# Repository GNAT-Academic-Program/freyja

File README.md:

# Freyja

An FPGA development board intended to remove the setup work between an idea
and a working project: independent memory ports, a USB board controller,
observable power rails and keyed extension connectors.

The repository is **Freyja**; the current hardware stamp is **FREYA HW
0.1.0-proto.1**, with **XC7A100T-2FGG676I + RP2350B**. Identity comes from
[`tools/identity.py`](tools/identity.py). The KiCad basename `odin` and imported
library names are retained for compatibility; they do not identify another
active project.

## Open the current project

Open **[`kicad/odin.kicad_pro`](kicad/odin.kicad_pro)** in KiCad 9.
[`kicad/odin.kicad_pcb`](kicad/odin.kicad_pcb) owns placement and routing;
[`kicad/odin.kicad_sch`](kicad/odin.kicad_sch) is the generated root schematic.
See [the project map](kicad/README.md) and the single
[current workflow](ref/ide-agent-prompt.md) before editing or regenerating.

The board is 100 × 140 mm with eight copper layers and 524 parts, each in the
netlist and placed on the PCB, the four mounting holes H1–H4 included. All
assembly is on F.Cu. **Routing is unfinished.** All four PSRAM ports, their
ground connections and return stitching, the `+1V8_IO` distribution, the SDRAM,
the four HDMI pairs, LINK P and Q, the four Ethernet pairs and U30's local supplies,
straps and crystal are on the board, and since 2026-11-09 the regulator cells
U11 to U15, the `+1V0`, `+1V8`, `+2V5`, `VCCIO_1` and `VCCIO_2` distributions,
U34's source-select cell with its control lines, the `+5V` distribution and
its monitor, and the power-input tree (J50 and USB-C to `VSYS`, `VBUS` to U26
and U34, `VSYS` to U11 and U12, U26's and U18's islands), and since 2026-11-10 the
board controller's bring-up set (U7's regulator, crystal, flash, +3V3 and +1V1, the
USB data pair, the supervisor JTAG and sideband, the FPGA configuration straps
and configuration flash, the system clock), then its leftovers (SWD, RUN, UART, heartbeat LED, the USB
TVS, `EXT_EN` to U22), the `DBG_TCK`/`DBG_TDO` and FPGA-to-supervisor UART links, and every `+3V3` and ground
plane connection, then the first FPGA escape batch: the UART's receive line (on a moved ball), the microSD
and MRAM pull-ups with two lines of each to the FPGA, both buffered buses' connector side and three lines of
bus 1's FPGA side, HDMI management and `MON_2V5`; then the signal batch on a revised allocation: 43 of the 48
slot E to H lines (E/F and G/H trade ball rows in bank 34), `HDMI_SDA` (on a moved ball), the whole microSD
and debug JTAG links and `MRAM_SI`, and bus 1's connector side but two lines (U10's channels reversed).
Slots A to D, both buses' FPGA side, `MRAM_CS` and `MON_3V3` remain open: the west half of the FPGA has no
way out past the finished memory and `VCCIO_1` routes, and moving the nine SDRAM address lanes was tried and
does not fit. Counts, the per-face escape results, the leftovers with their alternatives and open issues are in
[current findings](findings.md). The gate reports DRC and unrouted items
without gating them, so a passing gate is not a fabrication pass.

Historical baseline, 2026-11-03 cleanup at `3f76447`, before any routing: zero
tracks and vias, 499 unrouted items listed, DRC zero errors and 313 warnings,
zero schematic-parity issues. Independent import/connector checks had
pre-existing failures, listed in the findings.

## Work and validate

Run from the repository root with Python 3, KiCad CLI/pcbnew 9 and PyYAML:

```sh
python3 tools/alloc.py --check
python3 tools/gate.py --strict
python3 tools/audit_easyeda.py
python3 tools/check_connector_rework.py
git diff --check
```

The gate reports DRC/unrouted counts without failing on them. Read the report
and independent checker results. [The workflow](ref/ide-agent-prompt.md)
explains exact ERC expectations, scratch DRC reports, file ownership,
generator writes and the cleanup checkpoint after several routing chunks.
Documentation cleanup must preserve hardware contents. Never use
`tools/gen_pcb.py` without `--rules-only` on the existing board.

Circuit ownership is [`tools/design.py`](tools/design.py); FPGA allocation is
[`tools/alloc.py`](tools/alloc.py). The project uses generated `odin:` libraries,
stock KiCad libraries, and **active imported `EasyEDA:` symbols, footprints and
3D models under [`easyeda/`](easyeda/)**. Preserve their identifiers and exact
qualified land patterns.

## Design intent

Four independent QSPI PSRAM links provide 32 MB without forcing a project to
start with a DDR controller; a 32 MB SDRAM provides another memory option.
The RP2350B is the board controller for configuration, power control and
readback. Eight direct extension sections and two buffered sections expose
documented signals and rails. ETH, raw LVDS LINK P/Q and HDMI are present in
the current circuit. Firmware, timing and operating performance still require
their own validation; PCB/ERC checks alone do not establish them.

For future decisions, keep the original test: **does this remove work that
was never the point, or add work that looks like the point?** Prefer explicit
limits, direct wiring and references an extension builder can understand.

## Supporting references

- [User manual](ref/user-manual.md), [extension connector contract](ref/extension-ux.md) and [worked Gameboy extension](ref/gameboy-extension.md).
- [Parts guide](ref/parts-guide.md), [qualified parts](ref/qualified-parts.md), [power budget](ref/power-budget.md), [assembly/import checklist](ref/jlcpcb-import-checklist.md) and [BOM](ref/bom-jlcpcb.csv).
- [Power input](ref/power-input.md), [power tree](ref/power.md), [PSRAM](ref/psram.md), [controller flash](ref/supervisor-flash.md), [network](ref/network.md) and [raw LVDS links](ref/link-ports.md).
- [Mechanical intent and history](floorplan.md), [FPGA decoupling](ref/decoupling.md), [island layout rationale](ref/island-layouts.md), [impedance/stackup](ref/pcb-impedance.md) and [local datasheets](ref/datasheets/).
- [SDRAM profile, 100 MHz CL3](gateware/sdram100/README.md): implementation contract, timing fixture and constraints, separate from the allocation gate.
- [RGMII profile, 1000 Mb/s](gateware/rgmii1000/README.md): timing contract, fixture and constraints for U30, separate from the allocation gate.
- [Current status and chronological findings](findings.md). Its older numbered findings are dated history, not a fresh open-task list.
- [Archive index and provenance](archive/README.md): old Altium/EasyEDA exports, extraction reports, superseded workflow/plans, dated review evidence and Vivado scratch outputs. [Salvage rationale](ref/salvage-from-odin0.md) retains useful earlier engineering decisions.

std::vector<int> a; --- stree

std::vector<int> b; --- forge

type int_vector std::vector<int, float>;

a: int_vector;
b: int_vector;

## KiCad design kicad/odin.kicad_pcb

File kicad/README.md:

# Current FREYA KiCad project

Open **[odin.kicad_pro](odin.kicad_pro)** in KiCad 9. The hardware is **FREYA
HW 0.1.0-proto.1**, XC7A100T-2FGG676I + RP2350B; `odin` is the retained project
basename. **[odin.kicad_pcb](odin.kicad_pcb) is the authoritative manual
layout.** Preserve its placement, routing, outline, zones and mounting holes.

Use the single [current workflow](../ref/ide-agent-prompt.md) for ownership,
checks, regeneration side effects and the recurring cleanup checkpoint.
[Current findings](../findings.md) records the measured baseline and known
check failures. The [root README](../README.md) links subsystem references.

## File map

| File | Role |
|---|---|
| `odin.kicad_pcb` | Live layout; not a disposable generator output. |
| `odin.kicad_pro`, `odin.kicad_dru` | Project settings/net classes and custom design rules. `gen_pcb.py --rules-only` rewrites generated rules plus PCB stackup/layers; it is not a read-only check. |
| `odin.kicad_sch` | Root schematic generated by `tools/gen_project.py` from `tools/design.py`. |
| `fpga.kicad_sch` | FPGA, decoupling and configuration straps. |
| `power.kicad_sch` | Input, source mux, regulators, AUX IN pass-through and monitoring. |
| `memory.kicad_sch` | Four independent 1.8 V PSRAMs, SDRAM, MRAM, microSD and configuration flash. |
| `supervisor.kicad_sch` | Board Controller sheet: RP2350B, USB-C and FPGA control. |
| `slots.kicad_sch` | Eight direct and two buffered sections, rail selection and branch protection. |
| `network.kicad_sch` | RTL8211FDI-CG gigabit PHY/ETH and raw LVDS LINK P/Q. |
| `video.kicad_sch` | HDMI output through TPD12S016. |
| `odin.net` | KiCad export of the generated schematic; PCB synchronization reads this file. |
| `odin.kicad_sym`, `odin.pretty/` | Generated custom project symbols/footprints. |
| `sym-lib-table`, `fp-lib-table` | Select the custom, imported and system libraries. |
| `odin.kicad_prl`, `fp-info-cache` | Retained local editor state/cache; not circuit or layout sources. |

Manual schematic arrangements and generated library edits are overwritten by
regeneration. Read the generator write map before using any writer.
**`tools/gen_pcb.py` without `--rules-only` is prohibited on this board.**
`load_pcb.py` preserves common footprint origins but changes parts/nets and
also runs the silkscreen writer; it does not certify routed copper preservation.

## Imported dependencies and setup

The tables point to **`../easyeda/EasyEDA.kicad_sym`** and
**`../easyeda/EasyEDA.pretty/`**. These are active, qualified imported
dependencies, including U1's FGG676 footprint. Models live in
`../easyeda/EasyEDA.3dshapes/`. Keep the `EasyEDA:` namespace and the exact
footprints. `tools/alloc.py`, `symlib.py`, `gen_kicad.py` and `load_pcb.py`
also reference those paths.

Imported model paths use a mixture of `${KIPRJMOD}`, `${KICAD_3RD_PARTY}` and
relative `easyeda/` paths. Where used, configure `KICAD_3RD_PARTY` to the
repository's `easyeda` directory in KiCad's path settings; it is unset in the
verification shell. Six of the live board's 39 distinct imported model paths
also name files absent from the repository even with that mapping (DFN-10,
ESOP-8, QFN-20, RJ45 L16.5, SMB L4.32 and WSON-8 L2.0). This is a pre-existing
3D-preview dependency gap. Relative `easyeda/` paths may require resolution
from the repository root. Cleanup preserves all model identifiers and files.
Stock symbols, footprints
and optional stock 3D models come from the KiCad installation. The small
`kicad/EasyEDA.*` copies remain in place; the project tables select the
`../easyeda/` versions. Do not treat their presence as another active project.

## Current layout and references

The outline is 100 × 140 mm with 2 mm corner chamfers, eight layers, ENIG,
nominal 1.6 mm, JLC08161H-1080A: S / GND / S / PWR / GND / S / GND / S. The PCB
has 524 footprints, one per netlist part (the mounting holes H1–H4 included since 2026-11-10), all origins in the
outline's bounding box and all assembly on F.Cu. Five zones: GND on In1/In4/In6,
and +3V3 plus the +1V0 island on In3. Routing is under way and unfinished;
current counts are in [findings](../findings.md). At the 2026-11-03 cleanup
baseline `3f76447` the board had no tracks or vias.

Read [impedance and routing constraints](../ref/pcb-impedance.md),
[floorplan/mechanical intent](../floorplan.md),
[island layouts](../ref/island-layouts.md),
[decoupling](../ref/decoupling.md) and
[parts guide](../ref/parts-guide.md) alongside the actual board. Planning SVGs
and city YAML are design aids, not current placement snapshots. RGMII's
0.125 mm geometry remains an estimate to confirm with the fabricator.

Run the [validation commands](../ref/ide-agent-prompt.md#checks-that-do-not-write-hardware)
from the repository root. Exact ERC expectation: zero errors and the two
`FPGA_DXP`/`FPGA_DXN` dangling-label warnings, enforced by `tools/check_erc.py`.
The gate passes at the cleanup baseline, but DRC warnings/unrouted counts and
the independent checker failures still need review; see
[current findings](../findings.md). Dated verification counts and superseded
plans live in [the archive](../archive/README.md).

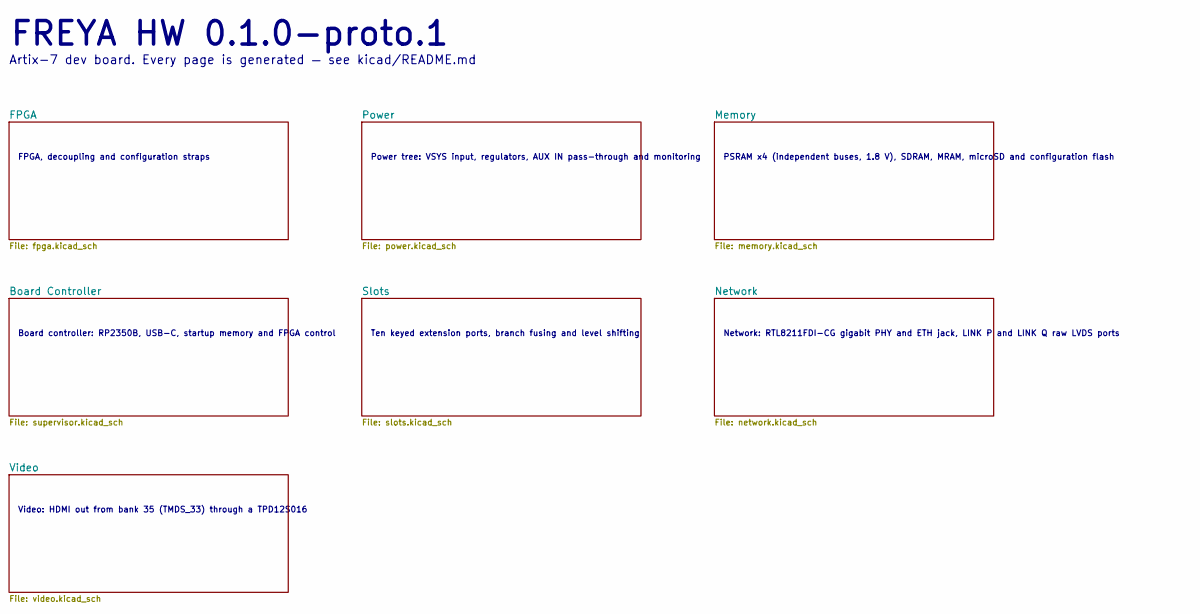
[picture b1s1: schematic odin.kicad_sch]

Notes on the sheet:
FREYA HW 0.1.0-proto.1
Artix-7 dev board. Every page is generated — see kicad/README.md
FPGA, decoupling and configuration straps
Power tree: VSYS input, regulators, AUX IN pass-through and monitoring
PSRAM x4 (independent buses, 1.8 V), SDRAM, MRAM, microSD and configuration flash
Board controller: RP2350B, USB-C, startup memory and FPGA control
Ten keyed extension ports, branch fusing and level shifting
Network: RTL8211FDI-CG gigabit PHY and ETH jack, LINK P and LINK Q raw LVDS ports
Video: HDMI out from bank 35 (TMDS_33) through a TPD12S016

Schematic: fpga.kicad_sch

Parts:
C246, C328: 100nF; C_0402_1005Metric; LCSC C1525
C301: 330uF 6.3V T520V337M006ATE025; CP_EIA-7343-31_Kemet-D; LCSC C136150
C302, C303, C304, C305, C306, C307, C320, C321, C322, C330, C331, C336, C337, C342, C343, C348, C349, C354, C355, C360, C361: 4.7uF 6.3V; C_0805_2012Metric
C308, C309, C310, C311, C312, C313, C314, C315, C317, C318, C323, C324, C325, C326, C327, C332, C333, C334, C335, C338, C339, C340, C341, C344, C345, C346, C347, C350, C351, C352, C353, C356, C357, C358, C359, C362, C363, C364, C365: 0.47uF 6.3V; C_0603_1608Metric
C316: 100uF 2.5V; C_1210_3225Metric
C319, C329, C366, C367, C368, C369, C394: 47uF 6.3V; C_1210_3225Metric
D1: F.0603.00025/P2-0603G1TS2-06T-002; LED0603-RD_GREEN; LCSC C7496818
Q4: BSS138LT1G; SOT-23-3_L2.9-W1.6-P1.90-LS2.8-BR; LCSC C82045
R1, R2, R3, R6: 1k; R_0402_1005Metric; LCSC C11702
R4, R5, R98, R203: 4.7k; R_0402_1005Metric; LCSC C25900
R7: 330; R_0402_1005Metric
R147: 33; R_0402_1005Metric; LCSC C25105
U1: XC7A100T-2FGG676I; FBGA-676_L27.0-W27.0-R26-C26-P1.00-BL; LCSC C1521803
X4: 50MHz CMOS; OSC-SMD_4P-L3.2-W2.5-BL; LCSC C717684

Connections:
+1V0: C301.1, C302.1, C303.1, C304.1, C305.1, C306.1, C307.1, C308.1, C309.1, C310.1, C311.1, C312.1, C313.1, C314.1, C315.1, C316.1, C317.1, C318.1, U1.J11 (VCCINT), U1.J13 (VCCINT), U1.K10 (VCCINT), U1.K12 (VCCINT), U1.L11 (VCCINT), U1.L13 (VCCINT), U1.M10 (VCCINT), U1.N13 (VCCBRAM), U1.P10 (VCCINT), U1.R13 (VCCBRAM), U1.T10 (VCCINT), U1.T12 (VCCINT), U1.U11 (VCCINT), U1.U13 (VCCBRAM), U1.V10 (VCCINT), U1.V12 (VCCINT), U1.W13 (VCCBRAM); also elsewhere on the board
+1V8: C319.1, C320.1, C321.1, C322.1, C323.1, C324.1, C325.1, C326.1, C327.1, C328.1, U1.J9 (VCCAUX), U1.L9 (VCCAUX), U1.M12 (VCCADC_0), U1.N9 (VCCAUX), U1.R9 (VCCAUX), U1.U9 (VCCAUX); also elsewhere on the board
+1V8_IO: C330.1, C331.1, C332.1, C333.1, C334.1, C335.1, C394.1, U1.AC25 (VCCO_13), U1.T16 (VCCO_13), U1.T26 (VCCO_13), U1.U23 (VCCO_13), U1.V20 (VCCO_13), U1.Y24 (VCCO_13); also elsewhere on the board
+2V5: C348.1, C349.1, C350.1, C351.1, C352.1, C353.1, C368.1, U1.A21 (VCCO_16), U1.B18 (VCCO_16), U1.C25 (VCCO_16), U1.D22 (VCCO_16), U1.E19 (VCCO_16), U1.F16 (VCCO_16); also elsewhere on the board
+3V3: C246.1, C329.1, C336.1, C337.1, C338.1, C339.1, C340.1, C341.1, C360.1, C361.1, C362.1, C363.1, C364.1, C365.1, C366.1, R1.1, R4.1, R5.1, R6.1, R7.1, R98.1, R203.1, U1.A1 (VCCO_35), U1.AA1 (VCCO_33), U1.AA21 (VCCO_12), U1.AB15 (CFGBVS_0), U1.AB18 (VCCO_12), U1.AC5 (VCCO_33), U1.AD2 (VCCO_33), U1.AD22 (VCCO_12), U1.AE19 (VCCO_12), U1.AF26 (VCCO_12), U1.C5 (VCCO_35), U1.D2 (VCCO_35), U1.F6 (VCCO_35), U1.G3 (VCCO_35), U1.J7 (VCCO_35), U1.K24 (VCCO_14), U1.L21 (VCCO_14), U1.N15 (VCCO_14), U1.N25 (VCCO_14), U1.P22 (VCCO_14), U1.R19 (VCCO_14), U1.U3 (VCCO_33), U1.W7 (VCCO_33), U1.W11 (VCCO_0), U1.W17 (VCCO_12), U1.Y4 (VCCO_33), U1.Y14 (VCCO_0), X4.1 (Tri-state), X4.4 (VDD); also elsewhere on the board
BUS5V0_DIR: U1.U24 (IO_0_13); also elsewhere on the board
BUS5V0_IO0: U1.V26 (IO_L2P_T0_13); also elsewhere on the board
BUS5V0_IO1: U1.W26 (IO_L2N_T0_13); also elsewhere on the board
BUS5V0_IO2: U1.AB26 (IO_L3P_T0_DQS_13); also elsewhere on the board
BUS5V0_IO3: U1.AC26 (IO_L3N_T0_DQS_13); also elsewhere on the board
BUS5V0_IO4: U1.U25 (IO_L1P_T0_13); also elsewhere on the board
BUS5V0_IO5: U1.U26 (IO_L1N_T0_13); also elsewhere on the board
BUS5V0_IO6: U1.W25 (IO_L4P_T0_13); also elsewhere on the board
BUS5V0_IO7: U1.Y26 (IO_L4N_T0_13); also elsewhere on the board
BUS5V0_OE_N: U1.V23 (IO_L10P_T1_13); also elsewhere on the board
BUS5V1_DIR: U1.U17 (IO_25_13); also elsewhere on the board
BUS5V1_IO0: U1.AC24 (IO_L9N_T1_DQS_13); also elsewhere on the board
BUS5V1_IO1: U1.AB24 (IO_L9P_T1_DQS_13); also elsewhere on the board
BUS5V1_IO2: U1.AB25 (IO_L7N_T1_13); also elsewhere on the board
BUS5V1_IO3: U1.Y25 (IO_L5P_T0_13); also elsewhere on the board
BUS5V1_IO4: U1.AA25 (IO_L5N_T0_13); also elsewhere on the board
BUS5V1_IO5: U1.V24 (IO_L6P_T0_13); also elsewhere on the board
BUS5V1_IO6: U1.W24 (IO_L6N_T0_VREF_13); also elsewhere on the board
BUS5V1_IO7: U1.AA24 (IO_L7P_T1_13); also elsewhere on the board
BUS5V1_OE_N: U1.W23 (IO_L10N_T1_13); also elsewhere on the board
CFG_CCLK: U1.H13 (CCLK_0); also elsewhere on the board
CFG_DONE: Q4.1 (G), R98.2, U1.W10 (DONE_0); also elsewhere on the board
CFG_INIT_B: R5.2, U1.V11 (INIT_B_0); also elsewhere on the board
CFG_M0: R1.2, U1.AB7 (M0_0)
CFG_M1: R2.1, U1.Y9 (M1_0)
CFG_M2: R3.1, U1.W9 (M2_0)
CFG_PROG_B: R4.2, U1.AE16 (PROGRAM_B_0); also elsewhere on the board
DBG_TCK: U1.N21 (IO_L13P_T2_MRCC_14); also elsewhere on the board
DBG_TDI: U1.M20 (IO_L8P_T1_D11_14); also elsewhere on the board
DBG_TDO: U1.L20 (IO_L8N_T1_D12_14); also elsewhere on the board
DBG_TMS: U1.N22 (IO_L13N_T2_MRCC_14); also elsewhere on the board
DONE_LED_A: D1.2 (A), R7.2
DONE_LED_K: D1.1 (C), Q4.3 (D)
FLASH_CS_B: R203.2, U1.P18 (IO_L6P_T0_FCS_B_14); also elsewhere on the board
FLASH_D0_MOSI: U1.R14 (IO_L1P_T0_D00_MOSI_14); also elsewhere on the board
FLASH_D1_MISO: U1.R15 (IO_L1N_T0_D01_DIN_14); also elsewhere on the board
FLASH_D2_WP: U1.P14 (IO_L2P_T0_D02_14); also elsewhere on the board
FLASH_D3_HOLD: U1.N14 (IO_L2N_T0_D03_14); also elsewhere on the board
FPGA_DXN: U1.R11 (DXN_0)
FPGA_DXP: U1.R12 (DXP_0)
GND: C246.2, C301.2, C302.2, C303.2, C304.2, C305.2, C306.2, C307.2, C308.2, C309.2, C310.2, C311.2, C312.2, C313.2, C314.2, C315.2, C316.2, C317.2, C318.2, C319.2, C320.2, C321.2, C322.2, C323.2, C324.2, C325.2, C326.2, C327.2, C328.2, C329.2, C330.2, C331.2, C332.2, C333.2, C334.2, C335.2, C336.2, C337.2, C338.2, C339.2, C340.2, C341.2, C342.2, C343.2, C344.2, C345.2, C346.2, C347.2, C348.2, C349.2, C350.2, C351.2, C352.2, C353.2, C354.2, C355.2, C356.2, C357.2, C358.2, C359.2, C360.2, C361.2, C362.2, C363.2, C364.2, C365.2, C366.2, C367.2, C368.2, C369.2, C394.2, Q4.2 (S), R2.2, R3.2, U1.A6 (GND), U1.A8 (GND), U1.A10 (GND), U1.A11 (MGTPRXN0_216), U1.A12 (GND), U1.A13 (MGTPRXN2_216), U1.A14 (GND), U1.A15 (MGTRREF_216), U1.A16 (GND), U1.A26 (GND), U1.AA6 (GND), U1.AA9 (GND), U1.AA10 (MGTAVCC_G10), U1.AA12 (MGTAVCC_G10), U1.AA14 (GND), U1.AA16 (GND), U1.AA26 (GND), U1.AB3 (GND), U1.AB8 (GND), U1.AB9 (GND), U1.AB10 (GND), U1.AB12 (GND), U1.AB14 (GND), U1.AB23 (GND), U1.AC7 (GND), U1.AC9 (MGTAVCC_G10), U1.AC11 (MGTAVCC_G10), U1.AC12 (MGTPRXP0_213), U1.AC13 (MGTAVCC_G10), U1.AC14 (MGTPRXP2_213), U1.AC15 (GND), U1.AC20 (GND), U1.AD6 (GND), U1.AD7 (MGTAVTT_G10), U1.AD9 (GND), U1.AD11 (GND), U1.AD12 (MGTPRXN0_213), U1.AD13 (GND), U1.AD14 (MGTPRXN2_213), U1.AD15 (MGTAVTT_G10), U1.AD16 (GND), U1.AE4 (GND), U1.AE6 (GND), U1.AE8 (MGTAVTT_G10), U1.AE10 (MGTAVTT_G10), U1.AE11 (MGTPRXP3_213), U1.AE12 (MGTAVTT_G10), U1.AE13 (MGTPRXP1_213), U1.AE14 (MGTAVTT_G10), U1.AE15 (GND), U1.AE24 (GND), U1.AF1 (GND), U1.AF6 (GND), U1.AF8 (GND), U1.AF10 (GND), U1.AF11 (MGTPRXN3_213), U1.AF12 (GND), U1.AF13 (MGTPRXN1_213), U1.AF14 (GND), U1.AF15 (MGTRREF_213), U1.AF16 (GND), U1.AF21 (GND), U1.B3 (GND), U1.B6 (GND), U1.B8 (MGTAVTT_G11), U1.B10 (MGTAVTT_G11), U1.B11 (MGTPRXP0_216), U1.B12 (MGTAVTT_G11), U1.B13 (MGTPRXP2_216), U1.B14 (MGTAVTT_G11), U1.B15 (GND), U1.B16 (GND), U1.B23 (GND), U1.C6 (GND), U1.C7 (MGTAVTT_G11), U1.C9 (GND), U1.C11 (GND), U1.C12 (MGTPRXN3_216), U1.C13 (GND), U1.C14 (MGTPRXN1_216), U1.C15 (MGTAVTT_G11), U1.C16 (GND), U1.C20 (GND), U1.D7 (GND), U1.D9 (MGTAVCC_G11), U1.D11 (MGTAVCC_G11), U1.D12 (MGTPRXP3_216), U1.D13 (MGTAVCC_G11), U1.D14 (MGTPRXP1_216), U1.D15 (GND), U1.D17 (GND), U1.E4 (GND), U1.E7 (GND), U1.E8 (GND), U1.E9 (GND), U1.E10 (GND), U1.E12 (GND), U1.E14 (GND), U1.E15 (GND), U1.E24 (GND), U1.F1 (GND), U1.F9 (GND), U1.F10 (MGTAVCC_G11), U1.F12 (MGTAVCC_G11), U1.F14 (GND), U1.F21 (GND), U1.G10 (GND), U1.G11 (GND), U1.G12 (GND), U1.G13 (GND), U1.G14 (VCCBATT_0), U1.G18 (GND), U1.H5 (GND), U1.H25 (GND), U1.J2 (GND), U1.J12 (GND), U1.J22 (GND), U1.K9 (GND), U1.K11 (GND), U1.K13 (GND), U1.K19 (GND), U1.L6 (GND), U1.L10 (GND), U1.L12 (GND), U1.L16 (GND), U1.L26 (GND), U1.M3 (GND), U1.M9 (GND), U1.M11 (GNDADC_0), U1.M13 (GND), U1.M23 (GND), U1.N10 (GND), U1.N11 (VREFN_0), U1.N12 (VP_0), U1.N20 (GND), U1.P7 (GND), U1.P9 (GND), U1.P11 (VN_0), U1.P12 (VREFP_0), U1.P13 (GND), U1.P17 (GND), U1.R4 (GND), U1.R10 (GND), U1.R24 (GND), U1.T1 (GND), U1.T9 (GND), U1.T11 (GND), U1.T13 (GND), U1.T21 (GND), U1.U8 (GND), U1.U10 (GND), U1.U12 (GND), U1.U18 (GND), U1.V5 (GND), U1.V13 (GND), U1.V15 (GND), U1.V25 (GND), U1.W2 (GND), U1.W12 (GND), U1.W22 (GND), U1.Y10 (GND), U1.Y11 (GND), U1.Y12 (GND), U1.Y13 (GND), U1.Y19 (GND), X4.2 (GND); also elsewhere on the board
HDMI_CEC: U1.B2 (IO_L19N_T3_VREF_35); also elsewhere on the board
HDMI_CLK_N: U1.A2 (IO_L20N_T3_35); also elsewhere on the board
HDMI_CLK_P: U1.A3 (IO_L20P_T3_35); also elsewhere on the board
HDMI_CT_HPD: U1.F2 (IO_L22P_T3_35); also elsewhere on the board
HDMI_D0_N: U1.B1 (IO_L21N_T3_DQS_35); also elsewhere on the board
HDMI_D0_P: U1.C1 (IO_L21P_T3_DQS_35); also elsewhere on the board
HDMI_D1_N: U1.D1 (IO_L23N_T3_35); also elsewhere on the board
HDMI_D1_P: U1.E1 (IO_L23P_T3_35); also elsewhere on the board
HDMI_D2_N: U1.A5 (IO_L15N_T2_DQS_35); also elsewhere on the board
HDMI_D2_P: U1.B5 (IO_L15P_T2_DQS_35); also elsewhere on the board
HDMI_HPD: U1.B4 (IO_L16P_T2_35); also elsewhere on the board
HDMI_LS_OE: U1.E2 (IO_L22N_T3_35); also elsewhere on the board
HDMI_SCL: U1.A4 (IO_L16N_T2_35); also elsewhere on the board
HDMI_SDA: U1.F4 (IO_L11N_T1_SRCC_35); also elsewhere on the board
JTAG_TCK: U1.H12 (TCK_0); also elsewhere on the board
JTAG_TDI: U1.H10 (TDI_0); also elsewhere on the board
JTAG_TDO: U1.J10 (TDO_0); also elsewhere on the board
JTAG_TMS: U1.H11 (TMS_0); also elsewhere on the board
LINK_P_RXC_N: U1.C18 (IO_L12N_T1_MRCC_16); also elsewhere on the board
LINK_P_RXC_P: U1.D18 (IO_L12P_T1_MRCC_16); also elsewhere on the board
LINK_P_RXD_N: U1.A18 (IO_L9N_T1_DQS_16); also elsewhere on the board
LINK_P_RXD_P: U1.A17 (IO_L9P_T1_DQS_16); also elsewhere on the board
LINK_P_TXC_N: U1.B26 (IO_L22N_T3_16); also elsewhere on the board
LINK_P_TXC_P: U1.C26 (IO_L22P_T3_16); also elsewhere on the board
LINK_P_TXD_N: U1.A24 (IO_L21N_T3_DQS_16); also elsewhere on the board
LINK_P_TXD_P: U1.A23 (IO_L21P_T3_DQS_16); also elsewhere on the board
LINK_Q_RXC_N: U1.D20 (IO_L14N_T2_SRCC_16); also elsewhere on the board
LINK_Q_RXC_P: U1.E20 (IO_L14P_T2_SRCC_16); also elsewhere on the board
LINK_Q_RXD_N: U1.A20 (IO_L15N_T2_DQS_16); also elsewhere on the board
LINK_Q_RXD_P: U1.B20 (IO_L15P_T2_DQS_16); also elsewhere on the board
LINK_Q_TXC_N: U1.A25 (IO_L20N_T3_16); also elsewhere on the board
LINK_Q_TXC_P: U1.B25 (IO_L20P_T3_16); also elsewhere on the board
LINK_Q_TXD_N: U1.A22 (IO_L17N_T2_16); also elsewhere on the board
LINK_Q_TXD_P: U1.B22 (IO_L17P_T2_16); also elsewhere on the board
MRAM_CS: U1.K25 (IO_L7P_T1_D09_14); also elsewhere on the board
MRAM_SCK: U1.K26 (IO_L7N_T1_D10_14); also elsewhere on the board
MRAM_SI: U1.L24 (IO_L9P_T1_DQS_14); also elsewhere on the board
MRAM_SO: U1.L25 (IO_L9N_T1_DQS_D13_14); also elsewhere on the board
PHY_INT_N: U1.G2 (IO_L24P_T3_35); also elsewhere on the board
PHY_MDC: U1.C17 (IO_L7P_T1_16); also elsewhere on the board
PHY_MDIO: U1.B17 (IO_L7N_T1_16); also elsewhere on the board
PHY_RESET_N: U1.G1 (IO_L24N_T3_35); also elsewhere on the board
PHY_RXC: U1.D19 (IO_L13P_T2_MRCC_16); also elsewhere on the board
PHY_RXD0: U1.C19 (IO_L13N_T2_MRCC_16); also elsewhere on the board
PHY_RXD1: U1.H17 (IO_0_16); also elsewhere on the board
PHY_RXD2: U1.E22 (IO_25_16); also elsewhere on the board
PHY_RXD3: U1.B19 (IO_L10P_T1_16); also elsewhere on the board
PHY_RX_CTL: U1.A19 (IO_L10N_T1_16); also elsewhere on the board
PHY_TXC: U1.C24 (IO_L23P_T3_16); also elsewhere on the board
PHY_TXD0: U1.B24 (IO_L23N_T3_16); also elsewhere on the board
PHY_TXD1: U1.C22 (IO_L19P_T3_16); also elsewhere on the board
PHY_TXD2: U1.C23 (IO_L19N_T3_VREF_16); also elsewhere on the board
PHY_TXD3: U1.C21 (IO_L16P_T2_16); also elsewhere on the board
PHY_TX_CTL: U1.B21 (IO_L16N_T2_16); also elsewhere on the board
PSRAM0_CE_B: U1.T15 (IO_L20N_T3_13); also elsewhere on the board
PSRAM0_IO0: U1.T17 (IO_L21P_T3_DQS_13); also elsewhere on the board
PSRAM0_IO1: U1.T18 (IO_L21N_T3_DQS_13); also elsewhere on the board
PSRAM0_IO2: U1.U15 (IO_L22P_T3_13); also elsewhere on the board
PSRAM0_IO3: U1.U16 (IO_L22N_T3_13); also elsewhere on the board
PSRAM0_SCK: U1.T14 (IO_L20P_T3_13); also elsewhere on the board
PSRAM1_CE_B: U1.V14 (IO_L23N_T3_13); also elsewhere on the board
PSRAM1_IO0: U1.V16 (IO_L24P_T3_13); also elsewhere on the board
PSRAM1_IO1: U1.V17 (IO_L24N_T3_13); also elsewhere on the board
PSRAM1_IO2: U1.V18 (IO_L19P_T3_13); also elsewhere on the board
PSRAM1_IO3: U1.W18 (IO_L19N_T3_VREF_13); also elsewhere on the board
PSRAM1_SCK: U1.U14 (IO_L23P_T3_13); also elsewhere on the board
PSRAM2_CE_B: U1.U19 (IO_L17N_T2_13); also elsewhere on the board
PSRAM2_IO0: U1.V19 (IO_L18P_T2_13); also elsewhere on the board
PSRAM2_IO1: U1.W19 (IO_L18N_T2_13); also elsewhere on the board
PSRAM2_IO2: U1.T20 (IO_L15P_T2_DQS_13); also elsewhere on the board
PSRAM2_IO3: U1.U20 (IO_L15N_T2_DQS_13); also elsewhere on the board
PSRAM2_SCK: U1.T19 (IO_L17P_T2_13); also elsewhere on the board
PSRAM3_CE_B: U1.Y20 (IO_L16N_T2_13); also elsewhere on the board
PSRAM3_IO0: U1.W21 (IO_L14P_T2_SRCC_13); also elsewhere on the board
PSRAM3_IO1: U1.Y21 (IO_L14N_T2_SRCC_13); also elsewhere on the board
PSRAM3_IO2: U1.Y22 (IO_L11P_T1_SRCC_13); also elsewhere on the board
PSRAM3_IO3: U1.Y23 (IO_L11N_T1_SRCC_13); also elsewhere on the board
PSRAM3_SCK: U1.W20 (IO_L16P_T2_13); also elsewhere on the board
PUDC_B: R6.2, U1.P15 (IO_L3P_T0_DQS_PUDC_B_14)
SB_UART_RX: U1.R18 (IO_25_14); also elsewhere on the board
SB_UART_TX: U1.P21 (IO_L14N_T2_SRCC_14); also elsewhere on the board
SDRAM_A0: U1.M26 (IO_L20N_T3_A07_D23_14); also elsewhere on the board
SDRAM_A1: U1.N26 (IO_L20P_T3_A08_D24_14); also elsewhere on the board
SDRAM_A2: U1.P26 (IO_L22N_T3_A04_D20_14); also elsewhere on the board
SDRAM_A3: U1.R26 (IO_L22P_T3_A05_D21_14); also elsewhere on the board
SDRAM_A4: U1.M25 (IO_L10N_T1_D15_14); also elsewhere on the board
SDRAM_A5: U1.P25 (IO_L19N_T3_A09_D25_VREF_14); also elsewhere on the board
SDRAM_A6: U1.R25 (IO_L19P_T3_A10_D26_14); also elsewhere on the board
SDRAM_A7: U1.T25 (IO_L21N_T3_DQS_A06_D22_14); also elsewhere on the board
SDRAM_A8: U1.M24 (IO_L10P_T1_D14_14); also elsewhere on the board
SDRAM_A9: U1.N24 (IO_L15N_T2_DQS_DOUT_CSO_B_14); also elsewhere on the board
SDRAM_A10: U1.P24 (IO_L17N_T2_A13_D29_14); also elsewhere on the board
SDRAM_A11: U1.T24 (IO_L21P_T3_DQS_14); also elsewhere on the board
SDRAM_A12: U1.N23 (IO_L15P_T2_DQS_RDWR_B_14); also elsewhere on the board
SDRAM_BA0: U1.P23 (IO_L17P_T2_A14_D30_14); also elsewhere on the board
SDRAM_BA1: U1.R23 (IO_L24N_T3_A00_D16_14); also elsewhere on the board
SDRAM_CAS_N: U1.F3 (IO_L18P_T2_35); also elsewhere on the board
SDRAM_CKE: U1.K6 (IO_L10N_T1_AD15N_35); also elsewhere on the board
SDRAM_CLK: U1.K7 (IO_L10P_T1_AD15P_35); also elsewhere on the board
SDRAM_CS_N: U1.D3 (IO_L17P_T2_35); also elsewhere on the board
SDRAM_DQ0: U1.E6 (IO_L1P_T0_AD4P_35); also elsewhere on the board
SDRAM_DQ1: U1.D6 (IO_L1N_T0_AD4N_35); also elsewhere on the board
SDRAM_DQ2: U1.H8 (IO_L2P_T0_AD12P_35); also elsewhere on the board
SDRAM_DQ3: U1.G8 (IO_L2N_T0_AD12N_35); also elsewhere on the board
SDRAM_DQ4: U1.H7 (IO_L3P_T0_DQS_AD5P_35); also elsewhere on the board
SDRAM_DQ5: U1.G7 (IO_L3N_T0_DQS_AD5N_35); also elsewhere on the board
SDRAM_DQ6: U1.F8 (IO_L4P_T0_35); also elsewhere on the board
SDRAM_DQ7: U1.F7 (IO_L4N_T0_35); also elsewhere on the board
SDRAM_DQ8: U1.H6 (IO_L5P_T0_AD13P_35); also elsewhere on the board
SDRAM_DQ9: U1.G6 (IO_L5N_T0_AD13N_35); also elsewhere on the board
SDRAM_DQ10: U1.H9 (IO_L6P_T0_35); also elsewhere on the board
SDRAM_DQ11: U1.G9 (IO_L6N_T0_VREF_35); also elsewhere on the board
SDRAM_DQ12: U1.J6 (IO_L7P_T1_AD6P_35); also elsewhere on the board
SDRAM_DQ13: U1.J5 (IO_L7N_T1_AD6N_35); also elsewhere on the board
SDRAM_DQ14: U1.L8 (IO_L8P_T1_AD14P_35); also elsewhere on the board
SDRAM_DQ15: U1.K8 (IO_L8N_T1_AD14N_35); also elsewhere on the board
SDRAM_LDQM: U1.J4 (IO_L9P_T1_DQS_AD7P_35); also elsewhere on the board
SDRAM_RAS_N: U1.C3 (IO_L17N_T2_35); also elsewhere on the board
SDRAM_UDQM: U1.H4 (IO_L9N_T1_DQS_AD7N_35); also elsewhere on the board
SDRAM_WE_N: U1.E3 (IO_L18N_T2_35); also elsewhere on the board
SD_CD: U1.T23 (IO_L24P_T3_A01_D17_14); also elsewhere on the board
SD_CS: U1.L22 (IO_L11P_T1_SRCC_14); also elsewhere on the board
SD_MISO: U1.R22 (IO_L23N_T3_A02_D18_14); also elsewhere on the board
SD_MOSI: U1.T22 (IO_L23P_T3_A03_D19_14); also elsewhere on the board
SD_SCK: U1.L23 (IO_L11N_T1_SRCC_14); also elsewhere on the board
SLOTA_IO0: U1.K15 (IO_L1P_T0_AD0P_15); also elsewhere on the board
SLOTA_IO1: U1.J16 (IO_L1N_T0_AD0N_15); also elsewhere on the board
SLOTA_IO2: U1.J14 (IO_L2P_T0_AD8P_15); also elsewhere on the board
SLOTA_IO3: U1.J15 (IO_L2N_T0_AD8N_15); also elsewhere on the board
SLOTA_IO4: U1.K16 (IO_L3P_T0_DQS_AD1P_15); also elsewhere on the board
SLOTA_IO5: U1.K17 (IO_L3N_T0_DQS_AD1N_15); also elsewhere on the board
SLOTA_IO6: U1.M14 (IO_L4P_T0_15); also elsewhere on the board
SLOTA_IO7: U1.L14 (IO_L4N_T0_15); also elsewhere on the board
SLOTA_IO8: U1.M15 (IO_L5P_T0_AD9P_15); also elsewhere on the board
SLOTA_IO9: U1.L15 (IO_L5N_T0_AD9N_15); also elsewhere on the board
SLOTA_IO10: U1.M16 (IO_L6P_T0_15); also elsewhere on the board
SLOTA_IO11: U1.M17 (IO_L6N_T0_VREF_15); also elsewhere on the board
SLOTB_IO0: U1.J19 (IO_L7P_T1_AD2P_15); also elsewhere on the board
SLOTB_IO1: U1.H19 (IO_L7N_T1_AD2N_15); also elsewhere on the board
SLOTB_IO2: U1.L17 (IO_L8P_T1_AD10P_15); also elsewhere on the board
SLOTB_IO3: U1.L18 (IO_L8N_T1_AD10N_15); also elsewhere on the board
SLOTB_IO4: U1.K20 (IO_L9P_T1_DQS_AD3P_15); also elsewhere on the board
SLOTB_IO5: U1.J20 (IO_L9N_T1_DQS_AD3N_15); also elsewhere on the board
SLOTB_IO6: U1.J18 (IO_L10P_T1_AD11P_15); also elsewhere on the board
SLOTB_IO7: U1.H18 (IO_L10N_T1_AD11N_15); also elsewhere on the board
SLOTB_IO8: U1.G20 (IO_L11P_T1_SRCC_15); also elsewhere on the board
SLOTB_IO9: U1.G21 (IO_L11N_T1_SRCC_15); also elsewhere on the board
SLOTB_IO10: U1.K21 (IO_L12P_T1_MRCC_15); also elsewhere on the board
SLOTB_IO11: U1.J21 (IO_L12N_T1_MRCC_15); also elsewhere on the board
SLOTC_IO0: U1.H21 (IO_L13P_T2_MRCC_15); also elsewhere on the board
SLOTC_IO1: U1.H22 (IO_L13N_T2_MRCC_15); also elsewhere on the board
SLOTC_IO2: U1.J23 (IO_L14P_T2_SRCC_15); also elsewhere on the board
SLOTC_IO3: U1.H23 (IO_L14N_T2_SRCC_15); also elsewhere on the board
SLOTC_IO4: U1.G22 (IO_L15P_T2_DQS_15); also elsewhere on the board
SLOTC_IO5: U1.F22 (IO_L15N_T2_DQS_ADV_B_15); also elsewhere on the board
SLOTC_IO6: U1.J24 (IO_L16P_T2_A28_15); also elsewhere on the board
SLOTC_IO7: U1.H24 (IO_L16N_T2_A27_15); also elsewhere on the board
SLOTC_IO8: U1.F23 (IO_L17P_T2_A26_15); also elsewhere on the board
SLOTC_IO9: U1.E23 (IO_L17N_T2_A25_15); also elsewhere on the board
SLOTC_IO10: U1.K22 (IO_L18P_T2_A24_15); also elsewhere on the board
SLOTC_IO11: U1.K23 (IO_L18N_T2_A23_15); also elsewhere on the board
SLOTD_IO0: U1.G24 (IO_L19P_T3_A22_15); also elsewhere on the board
SLOTD_IO1: U1.F24 (IO_L19N_T3_A21_VREF_15); also elsewhere on the board
SLOTD_IO2: U1.E25 (IO_L20P_T3_A20_15); also elsewhere on the board
SLOTD_IO3: U1.D25 (IO_L20N_T3_A19_15); also elsewhere on the board
SLOTD_IO4: U1.E26 (IO_L21P_T3_DQS_15); also elsewhere on the board
SLOTD_IO5: U1.D26 (IO_L21N_T3_DQS_A18_15); also elsewhere on the board
SLOTD_IO6: U1.H26 (IO_L22P_T3_A17_15); also elsewhere on the board
SLOTD_IO7: U1.G26 (IO_L22N_T3_A16_15); also elsewhere on the board
SLOTD_IO8: U1.G25 (IO_L23P_T3_FOE_B_15); also elsewhere on the board
SLOTD_IO9: U1.F25 (IO_L23N_T3_FWE_B_15); also elsewhere on the board
SLOTD_IO10: U1.J25 (IO_L24P_T3_RS1_15); also elsewhere on the board
SLOTD_IO11: U1.J26 (IO_L24N_T3_RS0_15); also elsewhere on the board
SLOTE_IO0: U1.U2 (IO_L18P_T2_34); also elsewhere on the board
SLOTE_IO1: U1.U1 (IO_L18N_T2_34); also elsewhere on the board
SLOTE_IO2: U1.U6 (IO_L21P_T3_DQS_34); also elsewhere on the board
SLOTE_IO3: U1.U5 (IO_L21N_T3_DQS_34); also elsewhere on the board
SLOTE_IO4: U1.T4 (IO_L16P_T2_34); also elsewhere on the board
SLOTE_IO5: U1.T3 (IO_L16N_T2_34); also elsewhere on the board
SLOTE_IO6: U1.T8 (IO_L24P_T3_34); also elsewhere on the board
SLOTE_IO7: U1.T7 (IO_L24N_T3_34); also elsewhere on the board
SLOTE_IO8: U1.T2 (IO_L17P_T2_34); also elsewhere on the board
SLOTE_IO9: U1.R2 (IO_L17N_T2_34); also elsewhere on the board
SLOTE_IO10: U1.T5 (IO_L20P_T3_34); also elsewhere on the board
SLOTE_IO11: U1.R5 (IO_L20N_T3_34); also elsewhere on the board
SLOTF_IO0: U1.R7 (IO_L23P_T3_34); also elsewhere on the board
SLOTF_IO1: U1.R6 (IO_L23N_T3_34); also elsewhere on the board
SLOTF_IO2: U1.R1 (IO_L15P_T2_DQS_34); also elsewhere on the board
SLOTF_IO3: U1.P1 (IO_L15N_T2_DQS_34); also elsewhere on the board
SLOTF_IO4: U1.R3 (IO_L13P_T2_MRCC_34); also elsewhere on the board
SLOTF_IO5: U1.P3 (IO_L13N_T2_MRCC_34); also elsewhere on the board
SLOTF_IO6: U1.R8 (IO_L22P_T3_34); also elsewhere on the board
SLOTF_IO7: U1.P8 (IO_L22N_T3_34); also elsewhere on the board
SLOTF_IO8: U1.P6 (IO_L19P_T3_34); also elsewhere on the board
SLOTF_IO9: U1.P5 (IO_L19N_T3_VREF_34); also elsewhere on the board
SLOTF_IO10: U1.P4 (IO_L14P_T2_SRCC_34); also elsewhere on the board
SLOTF_IO11: U1.N4 (IO_L14N_T2_SRCC_34); also elsewhere on the board
SLOTG_IO0: U1.N3 (IO_L12P_T1_MRCC_34); also elsewhere on the board
SLOTG_IO1: U1.N2 (IO_L12N_T1_MRCC_34); also elsewhere on the board
SLOTG_IO2: U1.N7 (IO_L5P_T0_34); also elsewhere on the board
SLOTG_IO3: U1.N6 (IO_L5N_T0_34); also elsewhere on the board
SLOTG_IO4: U1.N1 (IO_L9P_T1_DQS_34); also elsewhere on the board
SLOTG_IO5: U1.M1 (IO_L9N_T1_DQS_34); also elsewhere on the board
SLOTG_IO6: U1.M6 (IO_L6P_T0_34); also elsewhere on the board
SLOTG_IO7: U1.M5 (IO_L6N_T0_VREF_34); also elsewhere on the board
SLOTG_IO8: U1.M2 (IO_L11P_T1_SRCC_34); also elsewhere on the board
SLOTG_IO9: U1.L2 (IO_L11N_T1_SRCC_34); also elsewhere on the board
SLOTG_IO10: U1.M4 (IO_L3P_T0_DQS_34); also elsewhere on the board
SLOTG_IO11: U1.L4 (IO_L3N_T0_DQS_34); also elsewhere on the board
SLOTH_IO0: U1.M7 (IO_L2P_T0_34); also elsewhere on the board
SLOTH_IO1: U1.L7 (IO_L2N_T0_34); also elsewhere on the board
SLOTH_IO2: U1.L3 (IO_L8P_T1_34); also elsewhere on the board
SLOTH_IO3: U1.K2 (IO_L8N_T1_34); also elsewhere on the board
SLOTH_IO4: U1.L5 (IO_L4P_T0_34); also elsewhere on the board
SLOTH_IO5: U1.K5 (IO_L4N_T0_34); also elsewhere on the board
SLOTH_IO6: U1.K1 (IO_L7P_T1_34); also elsewhere on the board
SLOTH_IO7: U1.J1 (IO_L7N_T1_34); also elsewhere on the board
SLOTH_IO8: U1.K3 (IO_L1P_T0_34); also elsewhere on the board
SLOTH_IO9: U1.J3 (IO_L1N_T0_34); also elsewhere on the board
SLOTH_IO10: U1.H2 (IO_L10P_T1_34); also elsewhere on the board
SLOTH_IO11: U1.H1 (IO_L10N_T1_34); also elsewhere on the board
SYS_CLK: R147.2, U1.M21 (IO_L12P_T1_MRCC_14)
SYS_CLK_OSC: R147.1, X4.3 (OUTPUT)
VCCIO_1: C342.1, C343.1, C344.1, C345.1, C346.1, C347.1, C367.1, U1.F26 (VCCO_15), U1.G23 (VCCO_15), U1.H20 (VCCO_15), U1.J17 (VCCO_15), U1.K14 (VCCO_15), U1.M18 (VCCO_15); also elsewhere on the board
VCCIO_2: C354.1, C355.1, C356.1, C357.1, C358.1, C359.1, C369.1, U1.K4 (VCCO_34), U1.L1 (VCCO_34), U1.M8 (VCCO_34), U1.N5 (VCCO_34), U1.P2 (VCCO_34), U1.T6 (VCCO_34); also elsewhere on the board

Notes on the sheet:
FPGA — FPGA, decoupling and configuration straps — HW 0.1.0-proto.1
U1 FPGA
The FPGA is the board: every user design (a NEORV32 RISC-V core, a video pipeline, a protocol bridge) runs here. Its six user I/O banks are dedicated by job: bank 13 at 1.8 V carries the four PSRAMs and the two 5 V bus translators, bank 14 the configuration flash, the board-controller sideband, the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
decap VCCINT
Decoupling for VCCINT (+1V0), which powers the FPGA core logic; quantities from UG483 Table 2-2, row FGG676 / XC7A100T. Placement rule: ref/decoupling.md.
decap VCCBRAM
Decoupling for VCCBRAM (+1V0), which powers the FPGA block RAM; quantities from UG483 Table 2-2, row FGG676 / XC7A100T. Placement rule: ref/decoupling.md.
decap VCCAUX
Decoupling for VCCAUX (+1V8), which powers the FPGA auxiliary circuits (clocking, I/O pre-drivers); quantities from UG483 Table 2-2, row FGG676 / XC7A100T. Placement rule: ref/decoupling.md.
decap VCCADC
Decoupling for VCCADC (+1V8), which powers the FPGA's on-chip ADC (XADC); not in UG483 Table 2-2; one 100 nF bypass. Placement rule: ref/decoupling.md.
decap VCCO_0
Decoupling for VCCO_0 (+3V3), which powers configuration bank 0; quantities from UG483 Table 2-2, row FGG676 / XC7A100T. Placement rule: ref/decoupling.md.
decap VCCO_13
Decoupling for FPGA I/O bank 13's supply (VCCO): 2 x 4.7 uF and 4 x 0.47 uF, UG483 Table 2-2. They keep the bank's supply steady while its outputs switch. Placement rule: ref/decoupling.md.
decap VCCO_14
Decoupling for FPGA I/O bank 14's supply (VCCO): 2 x 4.7 uF and 4 x 0.47 uF, UG483 Table 2-2. They keep the bank's supply steady while its outputs switch. Placement rule: ref/decoupling.md.
decap VCCO_15
Decoupling for FPGA I/O bank 15's supply (VCCO): 2 x 4.7 uF and 4 x 0.47 uF, UG483 Table 2-2. They keep the bank's supply steady while its outputs switch. Placement rule: ref/decoupling.md.
decap VCCO_16
Decoupling for FPGA I/O bank 16's supply (VCCO): 2 x 4.7 uF and 4 x 0.47 uF, UG483 Table 2-2. They keep the bank's supply steady while its outputs switch. Placement rule: ref/decoupling.md.
decap VCCO_34
Decoupling for FPGA I/O bank 34's supply (VCCO): 2 x 4.7 uF and 4 x 0.47 uF, UG483 Table 2-2. They keep the bank's supply steady while its outputs switch. Placement rule: ref/decoupling.md.
decap VCCO_35
Decoupling for FPGA I/O bank 35's supply (VCCO): 2 x 4.7 uF and 4 x 0.47 uF, UG483 Table 2-2. They keep the bank's supply steady while its outputs switch. Placement rule: ref/decoupling.md.
decap VCCO group +3V3
Bulk capacitor shared by every FPGA I/O bank powered from +3V3: UG483 Table 2-2 note 3 asks one 47 uF per group of up to four banks on one voltage. See ref/decoupling.md.
decap VCCO group VCCIO_1
Bulk capacitor shared by every FPGA I/O bank powered from VCCIO_1: UG483 Table 2-2 note 3 asks one 47 uF per group of up to four banks on one voltage. See ref/decoupling.md.
decap VCCO group +2V5
Bulk capacitor shared by every FPGA I/O bank powered from +2V5: UG483 Table 2-2 note 3 asks one 47 uF per group of up to four banks on one voltage. See ref/decoupling.md.
decap VCCO group VCCIO_2
Bulk capacitor shared by every FPGA I/O bank powered from VCCIO_2: UG483 Table 2-2 note 3 asks one 47 uF per group of up to four banks on one voltage. See ref/decoupling.md.
decap VCCO group +1V8_IO
Bulk capacitor shared by every FPGA I/O bank powered from +1V8_IO: UG483 Table 2-2 note 3 asks one 47 uF per group of up to four banks on one voltage. See ref/decoupling.md.
config straps (UG470)
How the FPGA loads its design at power-on. M[2:0] = 001 selects master SPI: the FPGA clocks its bitstream out of the W25Q256 flash (U6) by itself. The mode straps are 1 k, the most UG470 v1.17 Table 2-4 allows. PROGRAM_B and INIT_B are pulled up so the board controller can restart configuration; PU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
X4 system clock
The FPGA's own clock. X4 runs at 50 MHz from power-on and enters bank 14 on a clock-capable (MRCC) ball, so it can feed an MMCM and make any frequency the design needs. Without it nothing in the fabric would run until a network link came up.
config flash
